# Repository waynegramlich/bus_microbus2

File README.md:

# bus_micorbus2
Bus module that connects to two MikroBus modules.

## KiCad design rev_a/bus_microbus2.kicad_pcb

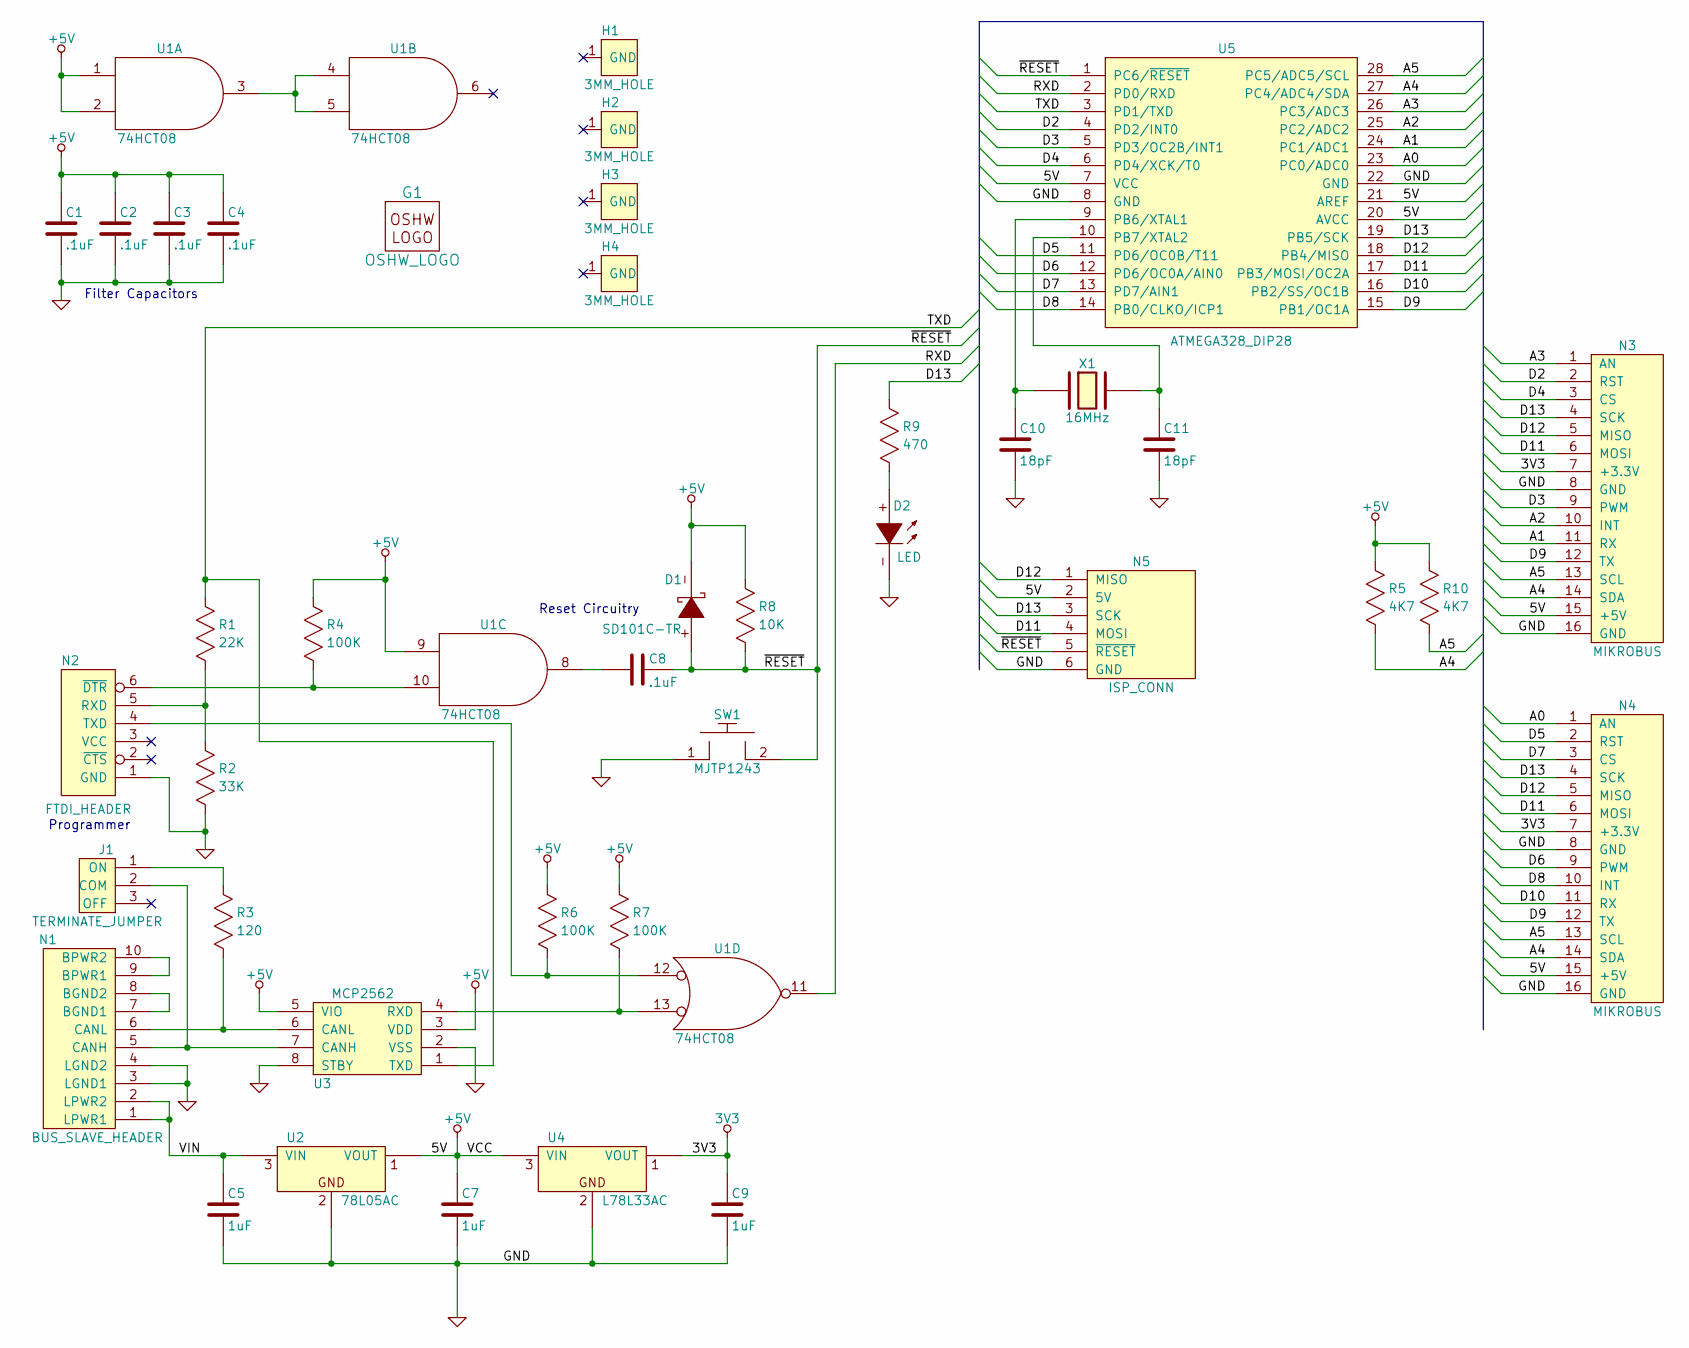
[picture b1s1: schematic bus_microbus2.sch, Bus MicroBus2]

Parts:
C1, C2, C3, C4, C8: .1uF; Capacitor3MMDiscRM2.5
C5, C7, C9: 1uF; Capacitor3MMDiscRM2.5
C10, C11: 18pF; Capacitor3MMDiscRM2.5
D1: SD101C-TR; Diode_DO-41_SOD81_Horizontal_RM10
D2: LED; T1_LED
G1: OSHW_LOGO; OSHW_LOGO_400mil
H1, H2, H3, H4: 3MM_HOLE; MountingHole_3mm
J1: TERMINATE_JUMPER; Pin_Header_Straight_1x03
N1: BUS_SLAVE_HEADER; Pin_Header_Straight_2x05_Shrouded
N2: FTDI_HEADER
N3, N4: MIKROBUS; mikrobus
N5: ISP_CONN; Pin_Header_Straight_2x03
R1: 22K; Resistor_Horizontal_400
R2: 33K; Resistor_Horizontal_400
R3: 120; Resistor_Horizontal_400
R4, R6, R7: 100K; Resistor_Horizontal_400
R5, R10: 4K7; Resistor_Horizontal_400
R8: 10K; Resistor_Horizontal_400
R9: 470; Resistor_Horizontal_400
SW1: MJTP1243; Button_6.5MM
U1: 74HCT08; DIP-14__300
U2: 78L05AC; TO92_123
U3: MCP2562; DIP-8__300
U4: L78L33AC; TO92_123
U5: ATMEGA328_DIP28
X1: 16MHz; Crystal_HC49-U_Vertical

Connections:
3V3: C9.1, N3.7 (+3.3V), N4.7 (+3.3V), U4.3 (VOUT)
+5V: C1.1, C2.1, C3.1, C4.1, C7.1, D1.-, N3.15 (+5V), N4.15 (+5V), N5.2 (5V), R4.2, R5.2, R6.2, R7.2, R8.2, R10.2, U1.1, U1.2, U1.9, U1.14 (VCC), U2.3 (VOUT), U3.3 (VDD), U3.5 (VIO), U4.1 (VIN), U5.7 (VCC), U5.20 (AVCC), U5.21 (AREF)
/A0: N4.1 (AN), U5.23 (PC0/ADC0)
/A1: N3.11 (RX), U5.24 (PC1/ADC1)
/A2: N3.10 (INT), U5.25 (PC2/ADC2)
/A3: N3.1 (AN), U5.26 (PC3/ADC3)
/A4: N3.14 (SDA), N4.14 (SDA), R5.1, U5.27 (PC4/ADC4/SDA)
/A5: N3.13 (SCL), N4.13 (SCL), R10.1, U5.28 (PC5/ADC5/SCL)
/D2: N3.2 (RST), U5.4 (PD2/INT0)
/D3: N3.9 (PWM), U5.5 (PD3/OC2B/INT1)
/D4: N3.3 (CS), U5.6 (PD4/XCK/T0)
/D5: N4.2 (RST), U5.11 (PD6/OC0B/T11)
/D6: N4.9 (PWM), U5.12 (PD6/OC0A/AIN0)
/D7: N4.3 (CS), U5.13 (PD7/AIN1)
/D8: N4.10 (INT), U5.14 (PB0/CLKO/ICP1)
/D9: N3.12 (TX), N4.12 (TX), U5.15 (PB1/OC1A)
/D10: N4.11 (RX), U5.16 (PB2/SS/OC1B)
/D11: N3.6 (MOSI), N4.6 (MOSI), N5.4 (MOSI), U5.17 (PB3/MOSI/OC2A)
/D12: N3.5 (MISO), N4.5 (MISO), N5.1 (MISO), U5.18 (PB4/MISO)
/D13: N3.4 (SCK), N4.4 (SCK), N5.3 (SCK), R9.2, U5.19 (PB5/SCK)
/RXD: U1.11, U5.2 (PD0/RXD)
/TXD: R1.2, U3.1 (TXD), U5.3 (PD1/TXD)
/VIN: C5.1, N1.1 (LPWR1), N1.2 (LPWR2), U2.1 (VIN)
/~RESET: C8.2, D1.+, N5.5 (~RESET), R8.1, SW1.2, U5.1 (PC6/~RESET)
GND: C1.2, C2.2, C3.2, C4.2, C5.2, C7.2, C9.2, C10.2, C11.2, D2.-, N1.3 (LGND1), N1.4 (LGND2), N2.1 (GND), N3.8 (GND), N3.16 (GND), N4.8 (GND), N4.16 (GND), N5.6 (GND), R2.1, SW1.1, U1.7 (GND), U2.2, U3.2 (VSS), U3.8 (STBY), U4.2, U5.8 (GND), U5.22 (GND)
unnamed: C8.1, U1.8
unnamed: C10.1, U5.9 (PB6/XTAL1), X1.1
unnamed: C11.1, U5.10 (PB7/XTAL2), X1.2
unnamed: D2.+, R9.1
unnamed: J1.1 (ON), R3.2
unnamed: J1.2 (COM), N1.5 (CANH), U3.7 (CANH)
unnamed: N1.6 (CANL), R3.1, U3.6 (CANL)
unnamed: N1.7 (BGND1), N1.8 (BGND2)
unnamed: N1.9 (BPWR1), N1.10 (BPWR2)
unnamed: N2.4 (TXD), R6.1, U1.12
unnamed: N2.5 (RXD), R1.1, R2.2
unnamed: N2.6 (~DTR), R4.1, U1.10
unnamed: R7.1, U1.13, U3.4 (RXD)
unnamed: U1.3, U1.4, U1.5

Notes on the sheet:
Filter Capacitors
Reset Circuitry
Programmer

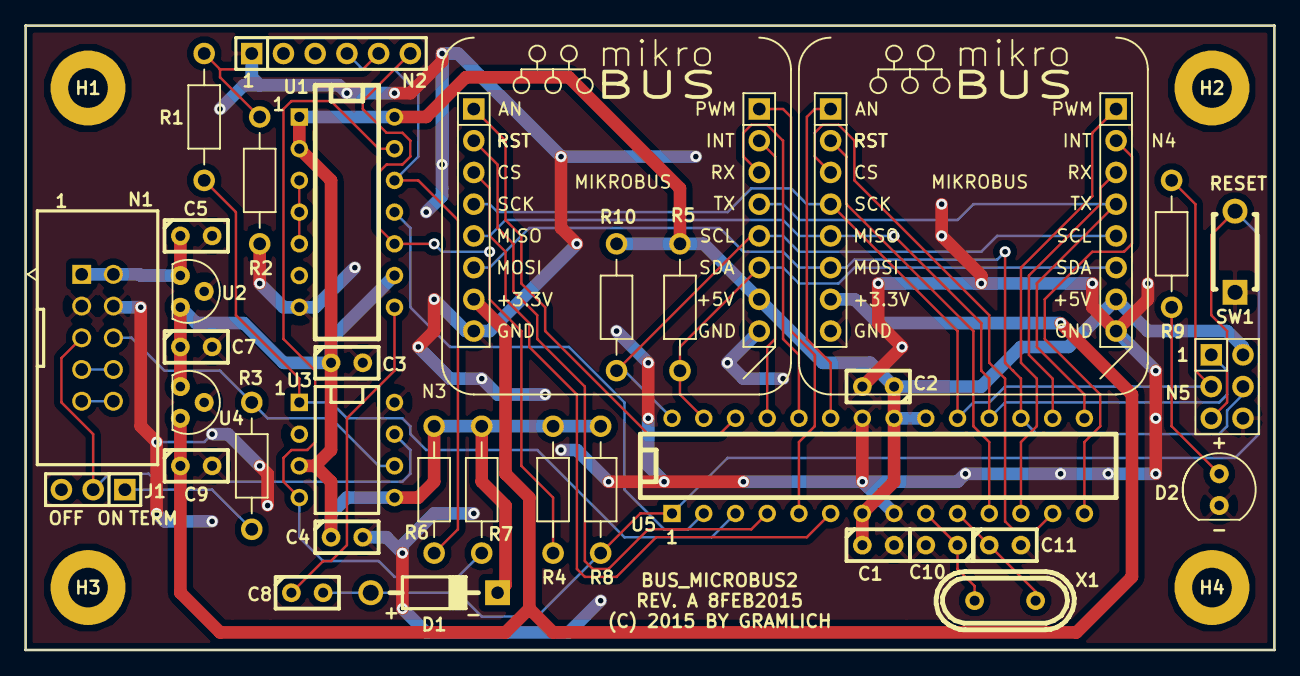
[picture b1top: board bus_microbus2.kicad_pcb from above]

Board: 2 copper layers, 100.0 x 50.0 mm, 40 parts (1 on the bottom side), 39 nets.

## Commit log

2015-02-09 Wrapped up Revision A.
2015-02-09 Mistyped the module name.

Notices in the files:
rev_a/bus_microbus2.kicad_pcb:
(C) 2015 BY GRAMLICH
